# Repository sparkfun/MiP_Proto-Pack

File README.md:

SparkFun MiP Proto-Pack
==============

[*SparkFun MiP Proto-Pack (DEV-13067)*](https://www.sparkfun.com/products/13067)

Prototyping backpack for the MiP

Repository Contents
-------------------

* **/Hardware** - Eagle design files (.brd, .sch)

Documentation
--------------
* **[Hookup Guide](https://learn.sparkfun.com/tutorials/hacking-the-mip---proto-pack)** - Basic hookup guide for the Proto-Pack.
* **[SparkFun Fritzing repo](https://github.com/sparkfun/Fritzing_Parts)** - Fritzing diagrams for SparkFun products.
* **[SparkFun 3D Model repo](https://github.com/sparkfun/3D_Models)** - 3D models of SparkFun products. 
* **[SparkFun Graphical Datasheets](https://github.com/sparkfun/Graphical_Datasheets)** -Graphical Datasheets for various SparkFun products.

License Information
-------------------

This product is _**open source**_! 

Please review the LICENSE.md file for license information. 

If you have any questions or concerns on licensing, please contact techsupport@sparkfun.com.

Distributed as-is; no warranty is given.

- Your friends at SparkFun.

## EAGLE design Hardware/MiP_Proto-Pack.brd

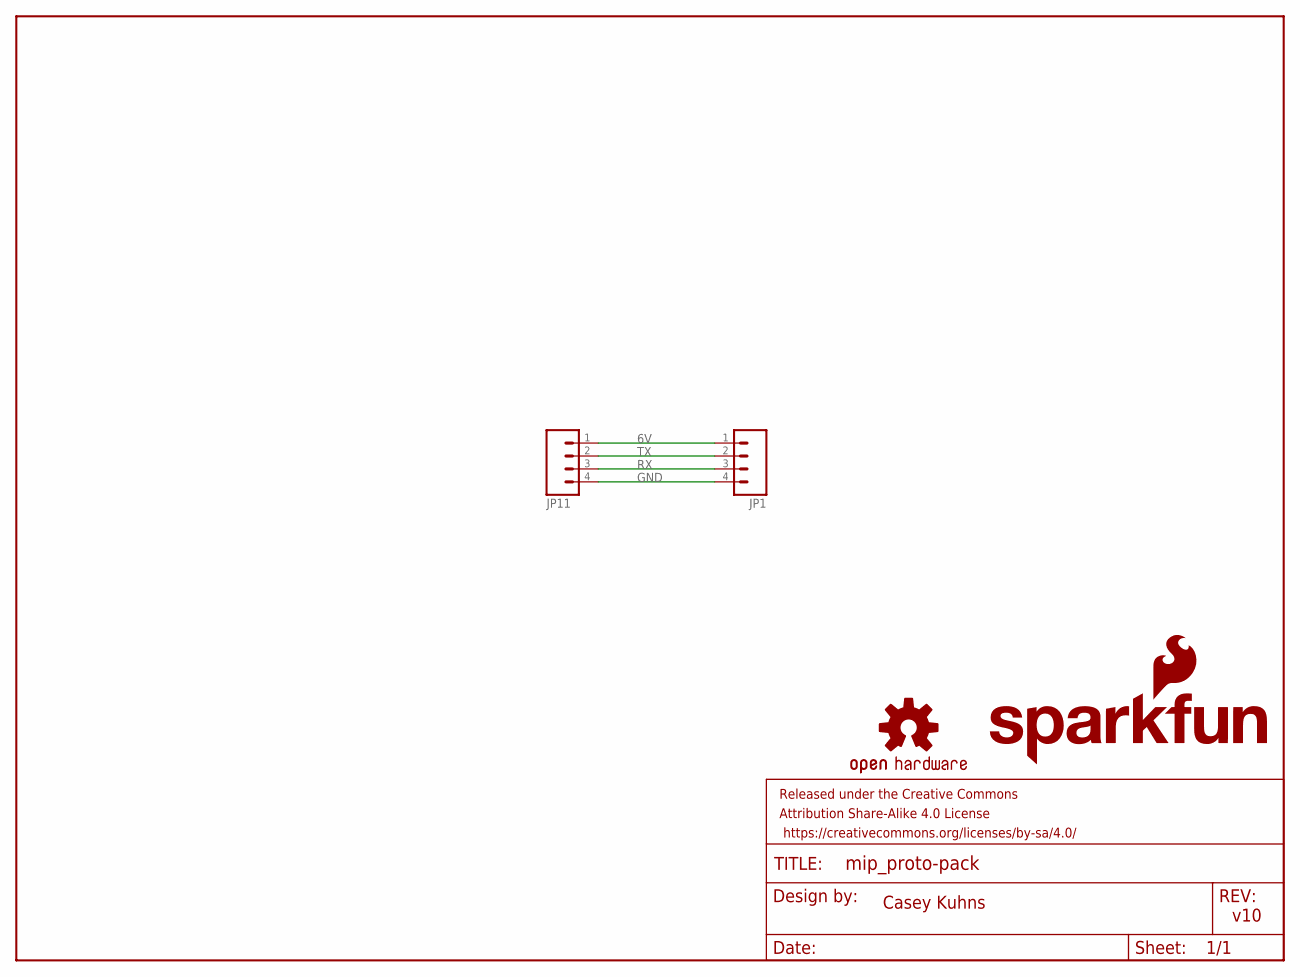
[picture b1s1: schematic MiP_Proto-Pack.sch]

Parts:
FRAME1: FRAME-LETTER; CREATIVE_COMMONS
JP1: M04PTH; 1X04
JP11: M04JST; 1X04-1.5MM_JST
LOGO1: SFE_LOGO_NAME_FLAME.1_INCH; SFE_LOGO_NAME_FLAME_.1
LOGO2: OSHW-LOGOS; OSHW-LOGO-S

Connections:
6V: JP1.1, JP11.1
GND: JP1.4, JP11.4
RX: JP1.3, JP11.3
TX: JP1.2, JP11.2

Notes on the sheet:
Casey Kuhns
v10

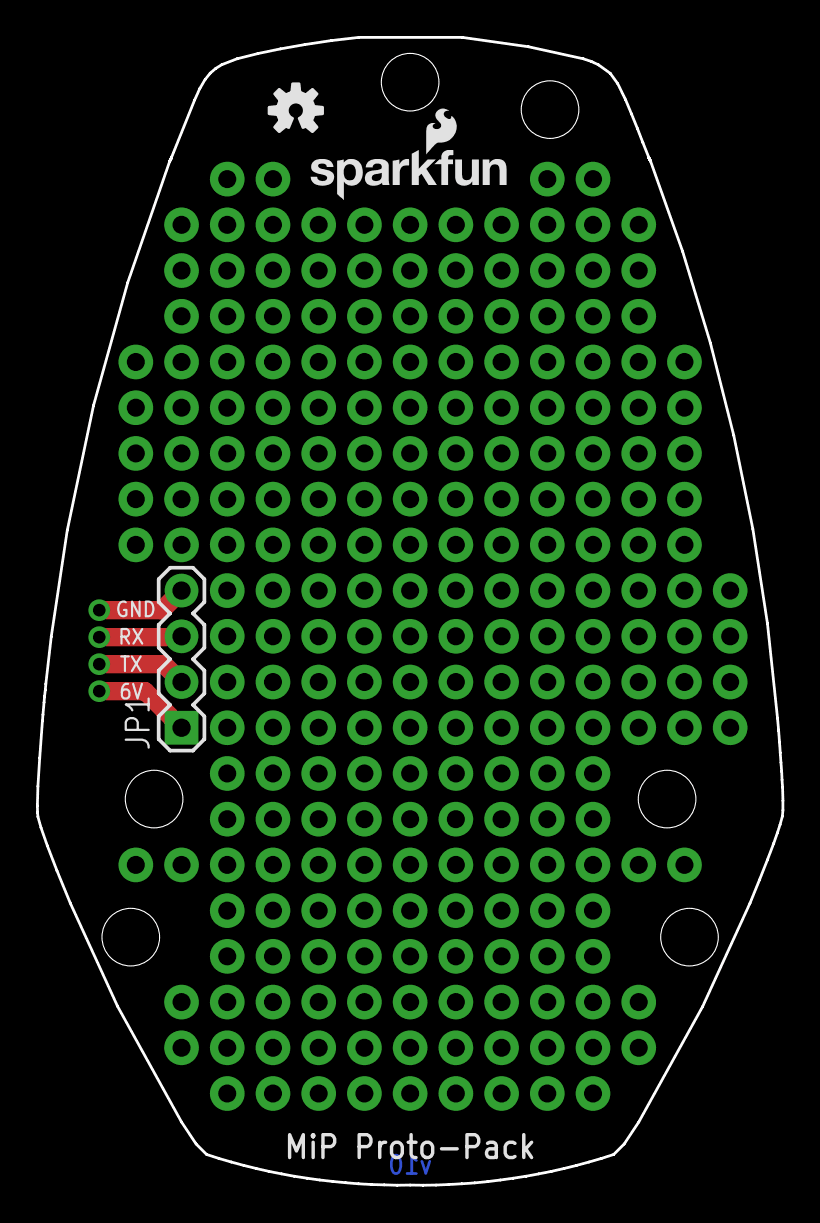
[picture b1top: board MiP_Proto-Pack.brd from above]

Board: 2 copper layers, 41.4 x 63.8 mm, 5 parts (1 on the bottom side), 4 nets.

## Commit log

2014-08-20 initial commit, Ready for review
2014-08-20 fixed labels
2014-10-06 corrected version number, added name to back of PCB
2014-12-05 Updated Readme.
2016-02-18 Adding license, updating README

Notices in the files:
parts and their libraries:
SparkFun-Aesthetics: Licensing: Creative Commons ShareAlike 4.0 International - https://creativecommons.org/licenses/by-sa/4.0
SparkFun-Aesthetics: Released under the Creative Commons Attribution Share-Alike 4.0 License
SparkFun-Aesthetics: https://creativecommons.org/licenses/by-sa/4.0
